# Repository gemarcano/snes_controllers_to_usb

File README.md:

# SNES Controllers to USB

This project contains the hardware design files and firmware used to build a 4
SNES controller hub to USB. At its core the board uses a Raspberry Pi Pico W
(could technically also be a regular Raspberry Pi Pico, but I have not tried
this) to poll the SNES controllers and manage USB communications with the host.

The design files are made using KiCAD, and the firmware is written in C++ using
the pico-sdk and FreeRTOS.

## Layout

The toplevel files are the hardware design files.

The software is in the `firmware/` directory. This has its own README.md.

The `graphics/` directory contains schematics and PCB diagrams in
easier-to-access formats for human use.

## Licenses

See the LICENSE files in the top level directory and in the `firmware/` folder
for more details.

In summary, the hardware files are released under the "CERN Open Hardware
Licence Version 2 - Weakly Reciprocal" license, and the software is
dual-licensed under the LGPL-2.1 or later and GPL-2.0 or later.

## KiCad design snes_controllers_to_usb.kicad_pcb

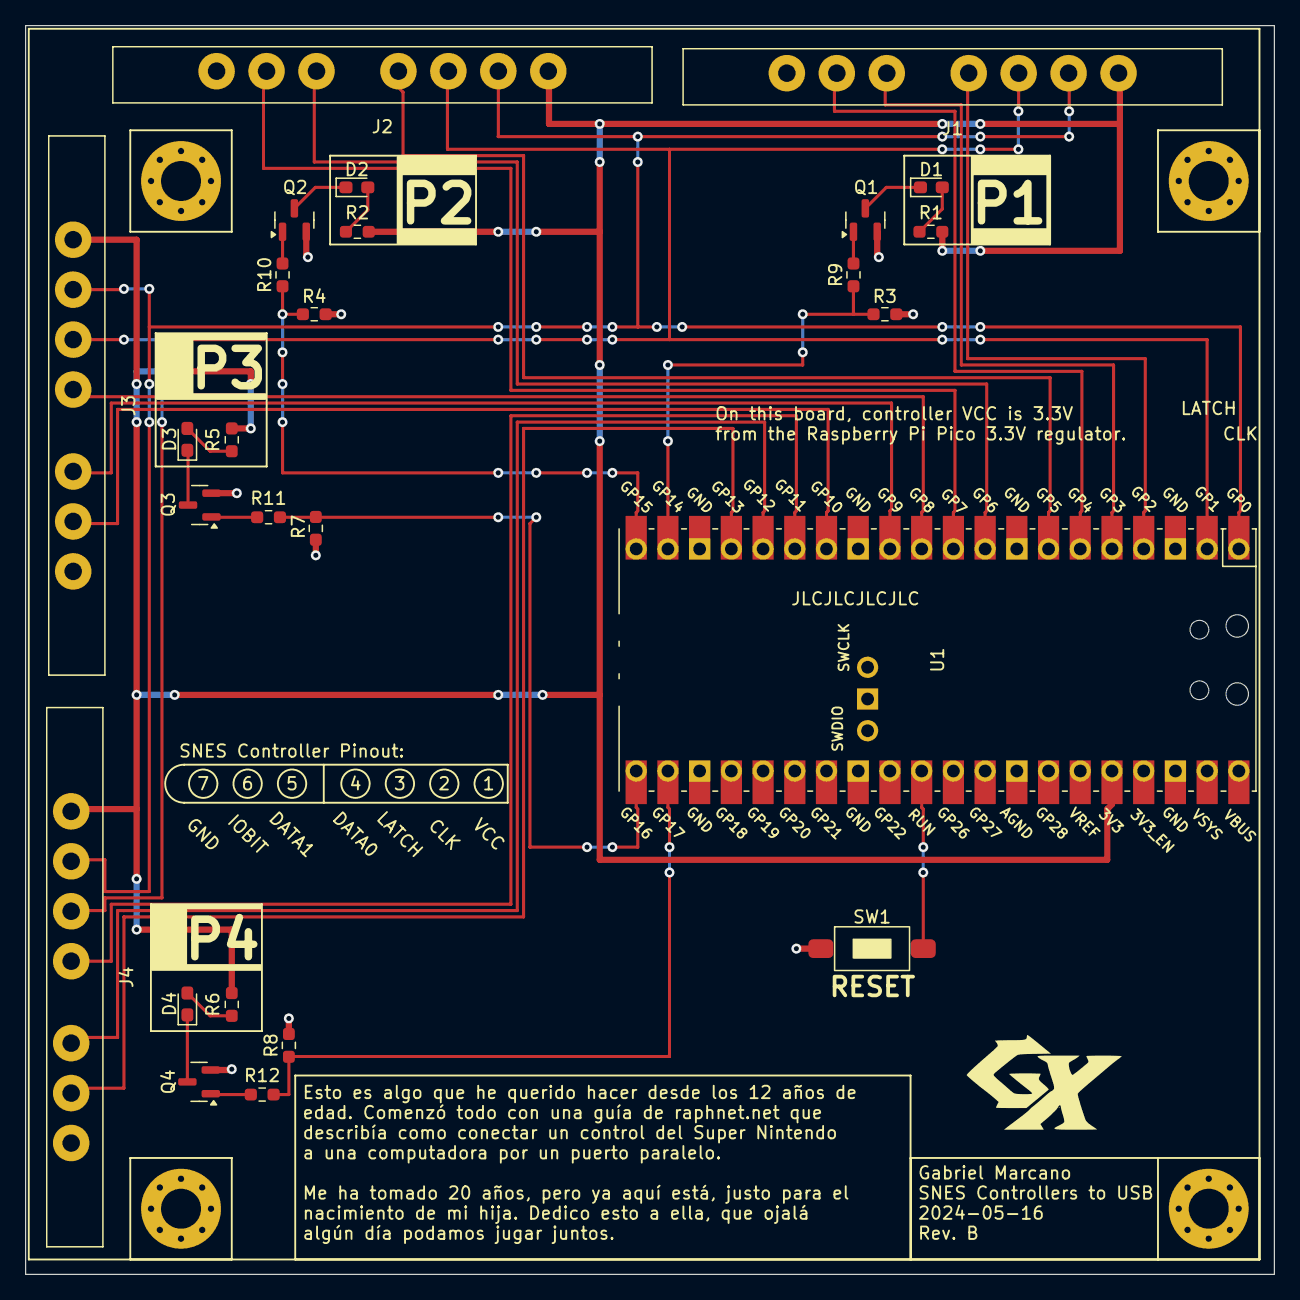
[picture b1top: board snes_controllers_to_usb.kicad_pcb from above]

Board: 2 copper layers, 100.0 x 100.0 mm, 30 parts (0 on the bottom side), 33 nets.

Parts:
D1, D2, D3, D4: Red LED, 2.0V; LED_0603_1608Metric_Pad1.05x0.95mm_HandSolder
H1, H2, H3, H4: MountingHole_Pad; MountingHole_3.2mm_M3_Pad_Via
J1, J2, J3, J4: SNES_controller_port; SNES_CONTROLLER_PORT_FEMALE_SHORT
Q1, Q2, Q3, Q4: BSS123; SOT-23
R1, R2, R5, R6: 260; R_0603_1608Metric_Pad0.98x0.95mm_HandSolder
R3, R4, R7, R8, R9, R10, R11, R12: 10k; R_0603_1608Metric_Pad0.98x0.95mm_HandSolder
SW1: RST_PUSH; PTS636_SM50_SMTR_LFS
U1: PicoW; RPi_PicoW_SMD_TH

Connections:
+3.3V: J1.1, J2.1, J3.1, J4.1, R1.1, R2.1, R5.1, R6.1, U1.36 (3V3)
/C0_CONN: R3.1, R9.1, U1.19 (GPIO14)
/C1_CONN: R4.1, R10.1, U1.20 (GPIO15)
/C2_CONN: R7.1, R11.1, U1.21 (GPIO16)
/C3_CONN: R8.1, R12.1, U1.22 (GPIO17)
/CLK: J1.2, J2.2, J3.2, J4.2, U1.1 (GPIO0)
/Data0_0: J1.4, U1.4 (GPIO2)
/Data0_1: J2.4, U1.7 (GPIO5)
/Data0_2: J3.4, U1.11 (GPIO8)
/Data0_3: J4.4, U1.15 (GPIO11)
/Data1_0: J1.5, U1.5 (GPIO3)
/Data1_1: J2.5, U1.9 (GPIO6)
/Data1_2: J3.5, U1.12 (GPIO9)
/Data1_3: J4.5, U1.16 (GPIO12)
/IOBit_0: J1.6, U1.6 (GPIO4)
/IOBit_1: J2.6, U1.10 (GPIO7)
/IOBit_2: J3.6, U1.14 (GPIO10)
/IOBit_3: J4.6, U1.17 (GPIO13)
/LATCH: J1.3, J2.3, J3.3, J4.3, U1.2 (GPIO1)
GND: H1.1, H2.1, H3.1, H4.1, J1.7, J2.7, J3.7, J4.7, Q1.2 (S), Q2.2 (S), Q3.2 (S), Q4.2 (S), R3.2, R4.2, R7.2, R8.2, SW1.1, U1.3 (GND), U1.8 (GND), U1.13 (GND), U1.18 (GND), U1.23 (GND), U1.28 (GND), U1.33 (AGND), U1.38 (GND), U1.42 (GND)
unnamed: D1.2 (A), R1.2
unnamed: D1.1 (K), Q1.3 (D)
unnamed: D2.2 (A), R2.2
unnamed: D2.1 (K), Q2.3 (D)
unnamed: D3.2 (A), R5.2
unnamed: D3.1 (K), Q3.3 (D)
unnamed: D4.2 (A), R6.2
unnamed: D4.1 (K), Q4.3 (D)
unnamed: Q1.1 (G), R9.2
unnamed: Q2.1 (G), R10.2
unnamed: Q3.1 (G), R11.2
unnamed: Q4.1 (G), R12.2
unnamed: SW1.2, U1.30 (RUN)

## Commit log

2024-02-10 Initial commit
    - Already at revision A*, minor text changes to text on PCB silk
    screen, renaming project from singular "snes controller" to plural
    "snes controllers"
2024-02-10 Add schematic and overall PCB pdfs
2024-02-15 Add beginnings of software implementation
    - Software is based off my wifi pc remote button code, as well as my
    old SNES STM32 controller converter code for the TinyUSB descriptor.
    - This code relies on the following upstream PRs:
    - https://github.com/raspberrypi/pico-sdk/pull/1530
    - https://github.com/FreeRTOS/FreeRTOS-Kernel/pull/991
    - https://github.com/raspberrypi/pico-sdk/pull/1635
2024-02-15 C++ify usb_descriptors, dynamic # of HID devices
    - Convert usb_descriptors to C++ to make it just overall easier to read
    - Much easier endian and utf16le handling
    - Add experimental support for reloading USB configuration if the
    number of controllers changes. Sometimes I'm seeing a crash on the
    debugger with an error of "ep %d %s was already available"
    - Support up to 4 controllers.
2024-02-16 Enable MPU to catch null-dereference
    - ROM exists at address 0x0, and while that's a valid memory to want to
    access... I don't need it. Set up the MPUs for both cores to block
    the first 256 bytes. This caught 2 bugs in TinyUSB :)
2024-02-17 Copy wifi management from pc_remote_button
    - Copy the improved wifi management code from pc_remote_button here,
    for further testing
    - Move wifi code to its own file
    - Copy status handling from pc_remote_button, more internet status now
    printed
2024-02-17 Cleanup, give better strings to interfaces
2024-02-19 wifi: Check for lwip flags as well for state
    - Apparently the pico cyw43 function can return JOIN status when LWIP
    reports the link is down. Check both to see if we need to reset the
    connection.
2024-02-19 usb: compute ID from pico ID
2024-02-21 Dual-core watchdog, refactor MPU init
    - Setup 3 watchdog tasks-- 1 per core, and a central one that
    aggregates status updates from the other two.
    - Refactor MPU initialization to a function
2024-02-21 Move watchdog routines to their own file
2024-02-23 add bkpt inst to pure virtual and terminate funcs
2024-02-23 Switch to heap_4
    - There's a race condition with heap_3 FreeRTOS between heap_3 and
    pico-sdk mutex implementation. See
    https://github.com/raspberrypi/pico-sdk/issues/1646 for more
    information.
2024-02-23 controller: virtual base class, random impl.
    - Made a virtual abstract base class for controllers, in preparation
    for the real hardware.
    - Implemented a random based controller using the new interface.
2024-02-26 First attempt at controller PIO
2024-02-27 Tested PIO implementation with oscillopscope
    - Found that I needed to change the default UART pins to not GPIO0 and
    1, as I'm using those for CLK and LATCH.
    - Added basic framework of a class to interact with the PIO control
2024-02-28 Connect PIO implementation with USB HID
    - Not using original controller abstract class
    - Add new usb_ functions to allow enabling and disabling of controllers
    based on a bitmask
    - use pio_controllers to poll controllers in HID task, and alert USB
    system if there's a change in connection state
2024-02-29 Change transistor gate resistors to 1kOhm
    - Currently by using both 10kOhm resistors for pulldown and the current
    limiting resistor, it effectively makes a voltage divider, which sets
    the gate voltage a little low. Change the current limiting resistor
    to 1kOhm to make the gate voltage be 90% of the input voltage, which
    should be good enough.
2024-02-29 Fix PIO timing for P2-4, add LED support
    - Timing for secondary PIO program was completely off, fix it and make
    each pulse take 15 cycles.
    - Add support for the LED GPIOs and have them turn on and off depending
    on the state of the controller detection.
2024-02-29 Add very basic cppcheck project file
2024-02-29 Address some concerns cppcheck found
    - Mostly setting single-argument constructors to explicit
    - Make sure to assign member variables when using default constructors
    - Use the proper PRIxx macros for printf'ing cstdint types
    - Use `zu` for printing size_t
2024-02-29 Start removing networking code
    - We're not using networking (yet?) for this project, so just rip out
    everything in main and tasks that use it. I'll remove the files in a
    future commit.
2024-02-29 Delete networking code
    - We don't yet need networking code for this project-- remove it and
    its support for now. We have a copy of it in
    https://github.com/gemarcano/pc_remote_button
2024-02-29 Update task stack usage based on actual usage
    - Most tasks now don't really use that much stack-- the minimum of 256
    stack units (really it's 256*4 bytes) is sufficient for all of the
    tasks I'm creating myself
2024-02-29 Enable MPU first, reduce timer task stack size
2024-03-06 CPU init tasks, refactoring of main
    - Made dedicated tasks for initializing CPU specific details (e.g.
    MPU).
    - Cleanups to main, including changing the function used to initialize
    tasks.
    - Moved stack overflow callback to FreeRTOS support.
    - Adjusted stack size for some tasks, was running into the stack
2024-03-06 Move project includes to "sctu" folder
    - Move our include to their own folder, just to make it far easier to
    identify when including them that they're ours.
2024-03-06 Refactor watchdog implementation
    - Use better FreeRTOS function to create tasks (includes core affinity)
    - Use atomic_bool instead of atomic_int as we're treating it as a bool
    anyway
    - Make sure lines aren't too long
2024-03-06 Add more documentation, refactor cdc
    - Move implementation for cdc_device to a file, not in the header.
    - Added documentation to most other headers.
    - Reduced the heap size of FreeRTOS to something closer to what it is
    actually using.
2024-03-07 Don't use stringstream to make unique ID
    - stringstream adds 14KB of code vs a simple loop approach to convert
    the ID from binary to UTF-8. As this only runs once, I don't need it
    to be fast, just right.
2024-03-07 Don't use std::format, uses 40kB of code!
    - std::format is really nice, but it uses an obscene amount of code
    (likely because a lot of it is dead, but can't be eliminated due to a
    lack of LTO since the pico-sdk doesn't support it). Manually generate
    the log strings instead.
    - Annoyingly enough, it looks like my newlib doesn't understand %zu for
    printf. Use %u instead (yes, not exactly the same, but should work
2024-03-12 firmware: add basic README
2024-03-12 Add basic overall README
2024-03-16 Refactor common code to gpico library
    - Refactored common code between my projects to gpico library, and
    delete redundant files.
    - New library is set up similar to how FreeRTOS and pico-sdk are setup.
    It has its own import cmake file, and it needs to know where it is.
2024-05-16 Update to KiCAD 8, revision B, move some resistors
    - Update schematic and PCB to KiCAD8
    - Move R7, R8, R9, and R10 so they no longer make a voltage divider at
    the transistor bases
    - Updated drawings
    - Replaced SNES port footprint with one where the silkscreen doesn't go
    past the end of the board
